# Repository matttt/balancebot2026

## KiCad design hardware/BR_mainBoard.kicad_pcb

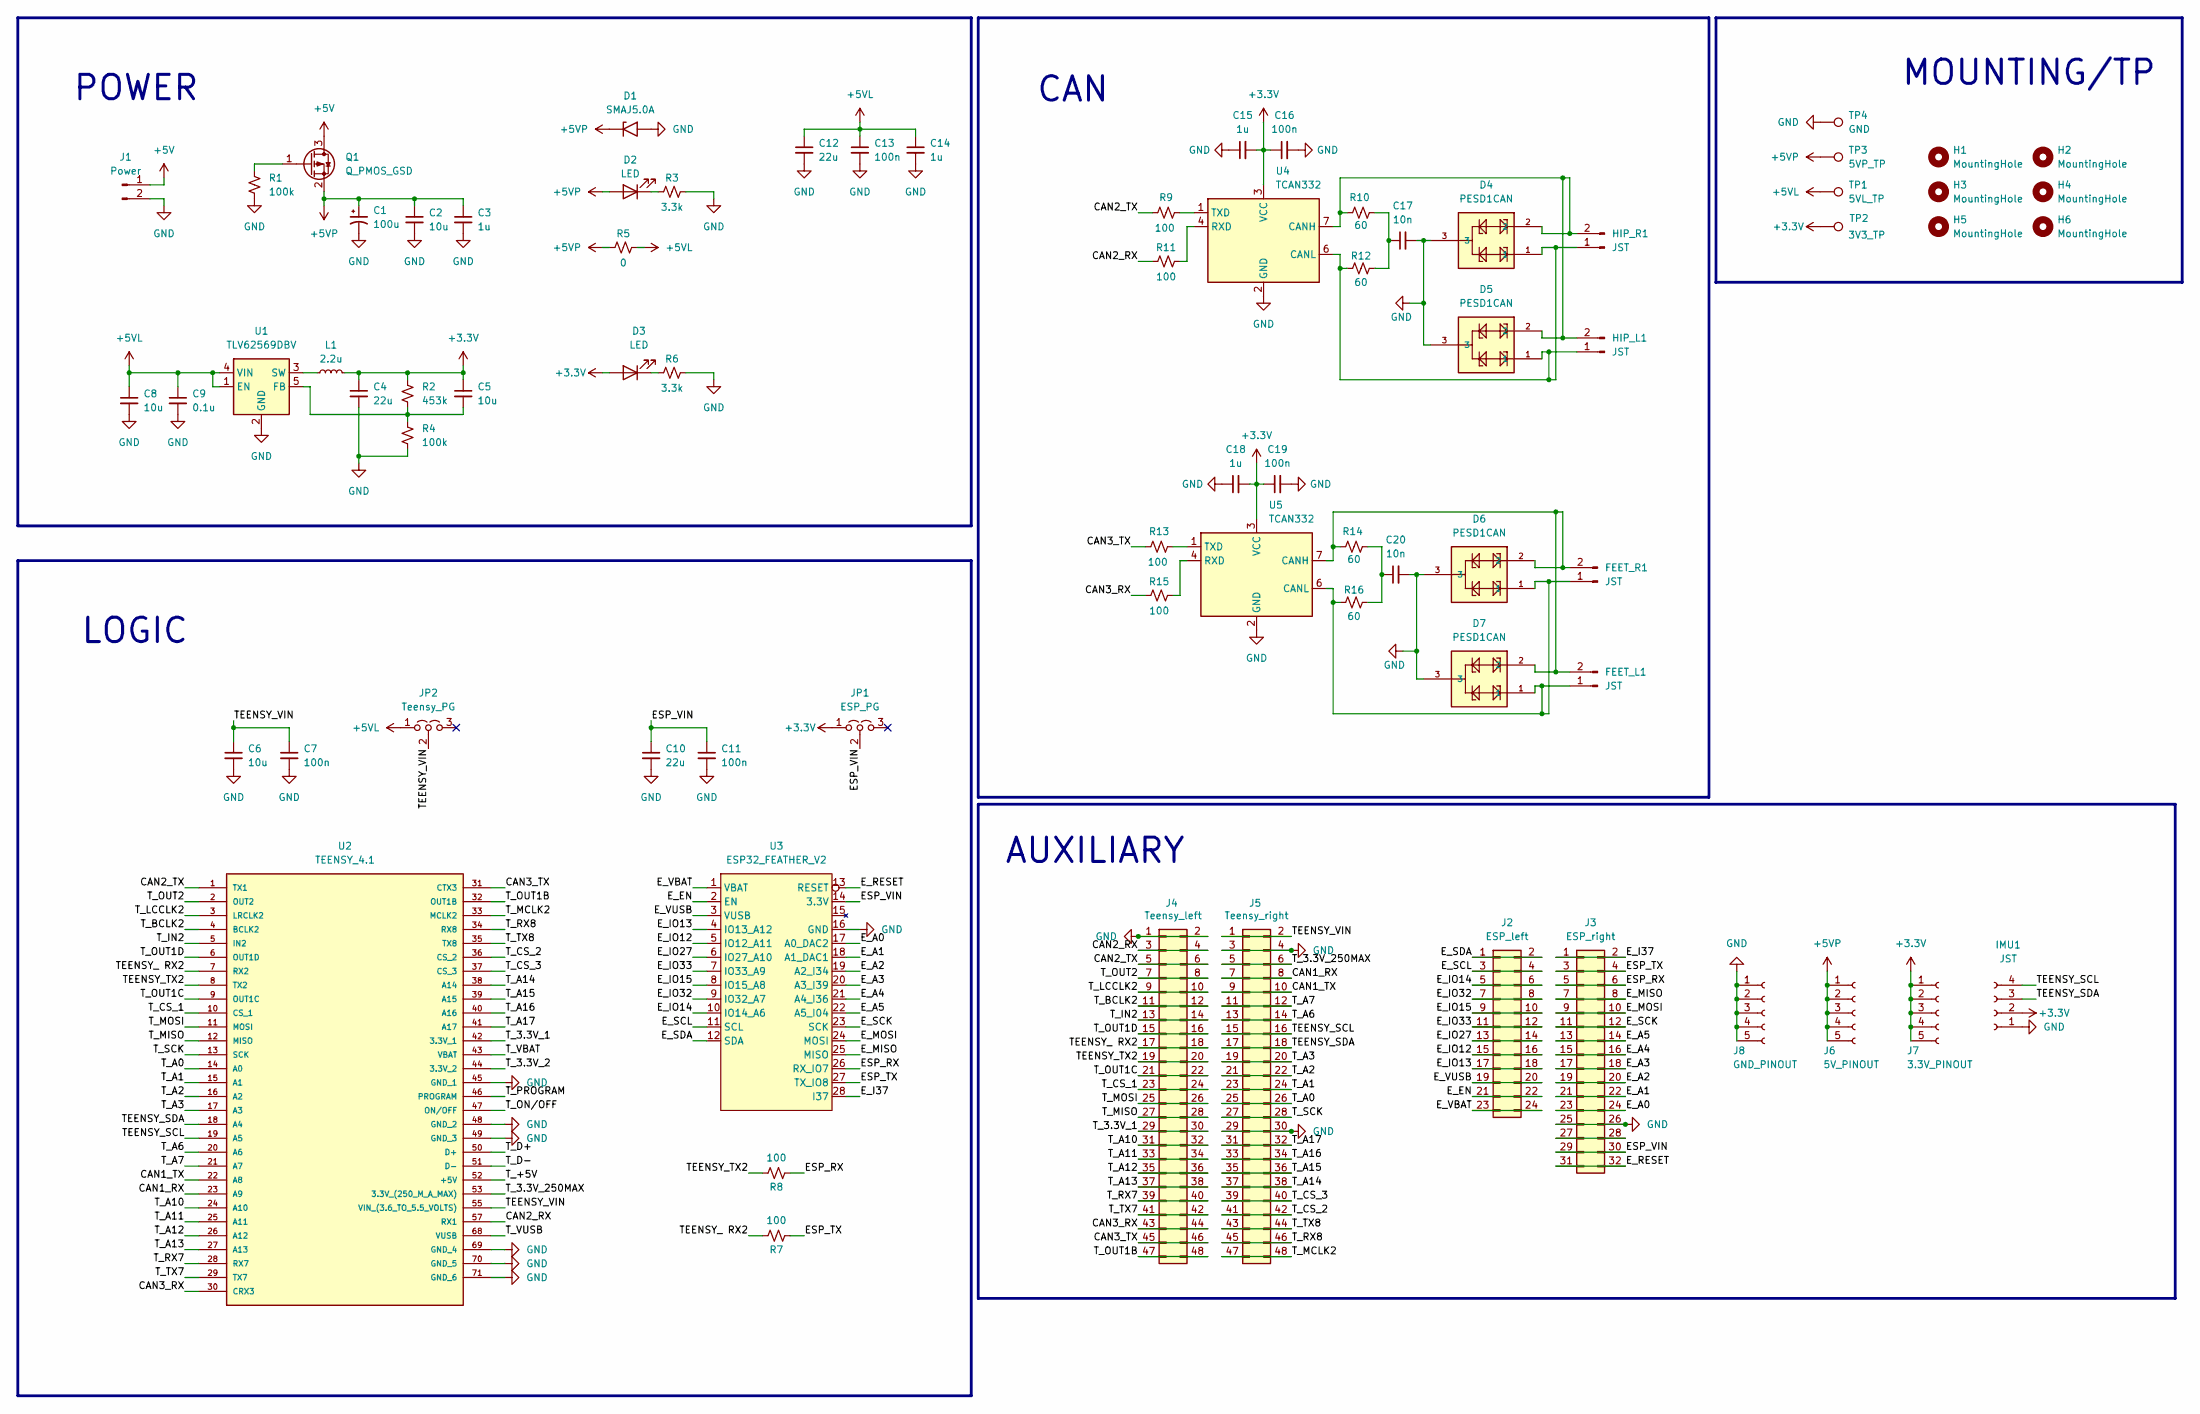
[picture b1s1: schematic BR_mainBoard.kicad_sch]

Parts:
C1: 100u; CP_Elec_6.3x5.4
C2, C5, C6, C8: 10u; C_1206_3216Metric
C3, C14, C15, C18: 1u; C_0805_2012Metric
C4, C10, C12: 22u; C_1206_3216Metric
C7, C11, C13, C16, C19: 100n; C_0805_2012Metric
C9: 0.1u; C_0805_2012Metric
C17, C20: 10n; C_0805_2012Metric
D1: SMAJ5.0A; D_SMA
D2, D3: LED; LED_0805_2012Metric
D4, D5, D6, D7: PESD1CAN; SOT-23
FEET_L1: JST; JST_VH_B2PS-VH_1x02_P3.96mm_Horizontal
FEET_R1: JST; JST_VH_B2PS-VH_1x02_P3.96mm_Horizontal
H1, H2, H3, H4, H5, H6: MountingHole; MountingHole_3.2mm_M3
HIP_L1: JST; JST_VH_B2PS-VH_1x02_P3.96mm_Horizontal
HIP_R1: JST; JST_VH_B2PS-VH_1x02_P3.96mm_Horizontal
IMU1: JST; JST_PH_S4B-PH-K_1x04_P2.00mm_Horizontal
J1: Power; JST_VH_B2P-VH-FB-B_1x02_P3.96mm_Vertical
J2: ESP_left; PinSocket_2x12_P2.54mm_Vertical
J3: ESP_right; PinSocket_2x16_P2.54mm_Vertical
J4: Teensy_left; PinSocket_2x24_P2.54mm_Vertical
J5: Teensy_right; PinSocket_2x24_P2.54mm_Vertical
J6: 5V_PINOUT; PinSocket_1x05_P2.54mm_Vertical
J7: 3.3V_PINOUT; PinSocket_1x05_P2.54mm_Vertical
J8: GND_PINOUT; PinSocket_1x05_P2.54mm_Vertical
JP1: ESP_PG; PinHeader_1x03_P2.54mm_Vertical
JP2: Teensy_PG; PinHeader_1x03_P2.54mm_Vertical
L1: 2.2u; L_Coilcraft_XAL4020-XXX
Q1: Q_PMOS_GSD; SOT-23
R1, R4: 100k; R_0805_2012Metric
R2: 453k; R_0805_2012Metric
R3, R6: 3.3k; R_0805_2012Metric
R5: 0; R_0805_2012Metric
R7, R8, R9, R11, R13, R15: 100; R_0805_2012Metric
R10, R12, R14, R16: 60; R_0603_1608Metric
TP1: 5VL_TP; TestPoint_Loop_D2.50mm_Drill1.0mm
TP2: 3V3_TP; TestPoint_Loop_D2.50mm_Drill1.0mm
TP3: 5VP_TP; TestPoint_Loop_D2.50mm_Drill1.0mm
TP4: GND; TestPoint_Loop_D2.50mm_Drill1.0mm
U1: TLV62569DBV; SOT-23-5
U2: TEENSY_4.1; TEENSY41; Manufacturer_Part_Number TEENSY 4.1
U3: ESP32_FEATHER_V2
U4, U5: TCAN332; SOIC-8_3.9x4.9mm_P1.27mm

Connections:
+3.3V: C4.1, C5.1, C15.2, C16.1, C18.2, C19.1, D3.2 (A), IMU1.2, J7.1, J7.2, J7.3, J7.4, J7.5, JP1.1 (A), L1.2, R2.1, TP2.1 (1_1), U4.3 (VCC), U5.3 (VCC)
+5V: J1.1, Q1.3 (D)
+5VL: C8.1, C9.1, C12.1, C13.1, C14.1, JP2.1 (A), R5.2, TP1.1 (1_1), U1.1 (EN), U1.4 (VIN)
+5VP: C1.1, C2.1, C3.1, D1.1 (A1), D2.2 (A), J6.1, J6.2, J6.3, J6.4, J6.5, Q1.2 (S), R5.1, TP3.1 (1_1)
/CAN1_RX: J5.7, J5.8, U2.23 (A9)
/CAN1_TX: J5.9, J5.10, U2.22 (A8)
/CAN2_RX: J4.3, J4.4, R11.1, U2.57 (RX1)
/CAN2_TX: J4.5, J4.6, R9.1, U2.1 (TX1)
/CAN3_RX: J4.43, J4.44, R15.1, U2.30 (CRX3)
/CAN3_TX: J4.45, J4.46, R13.1, U2.31 (CTX3)
/ESP_RX: J3.5, J3.6, R8.1, U3.26 (RX_IO7)
/ESP_TX: J3.3, J3.4, R7.1, U3.27 (TX_IO8)
/ESP_VIN: C10.1, C11.1, J3.29, J3.30, JP1.2 (C), U3.14 (3.3V)
/E_A0: J3.23, J3.24, U3.17 (A0_DAC2)
/E_A1: J3.21, J3.22, U3.18 (A1_DAC1)
/E_A2: J3.19, J3.20, U3.19 (A2_I34)
/E_A3: J3.17, J3.18, U3.20 (A3_I39)
/E_A4: J3.15, J3.16, U3.21 (A4_I36)
/E_A5: J3.13, J3.14, U3.22 (A5_I04)
/E_EN: J2.21, J2.22, U3.2 (EN)
/E_I37: J3.1, J3.2, U3.28 (I37)
/E_IO12: J2.15, J2.16, U3.5 (IO12_A11)
/E_IO13: J2.17, J2.18, U3.4 (IO13_A12)
/E_IO14: J2.5, J2.6, U3.10 (IO14_A6)
/E_IO15: J2.9, J2.10, U3.8 (IO15_A8)
/E_IO27: J2.13, J2.14, U3.6 (IO27_A10)
/E_IO32: J2.7, J2.8, U3.9 (IO32_A7)
/E_IO33: J2.11, J2.12, U3.7 (IO33_A9)
/E_MISO: J3.7, J3.8, U3.25 (MISO)
/E_MOSI: J3.9, J3.10, U3.24 (MOSI)
/E_RESET: J3.31, J3.32, U3.13 (RESET)
/E_SCK: J3.11, J3.12, U3.23 (SCK)
/E_SCL: J2.3, J2.4, U3.11 (SCL)
/E_SDA: J2.1, J2.2, U3.12 (SDA)
/E_VBAT: J2.23, J2.24, U3.1 (VBAT)
/E_VUSB: J2.19, J2.20, U3.3 (VUSB)
/TEENSY_ RX2: J4.17, J4.18, R7.2, U2.7 (RX2)
/TEENSY_SCL: IMU1.4, J5.15, J5.16, U2.19 (A5)
/TEENSY_SDA: IMU1.3, J5.17, J5.18, U2.18 (A4)
/TEENSY_TX2: J4.19, J4.20, R8.2, U2.8 (TX2)
/TEENSY_VIN: C6.1, C7.1, J5.1, J5.2, JP2.2 (C), U2.55 (VIN_(3.6_TO_5.5_VOLTS))
/T_3.3V_1: J4.29, J4.30, U2.42 (3.3V_1)
/T_3.3V_2: U2.44 (3.3V_2)
/T_3.3V_250MAX: J5.5, J5.6, U2.53 (3.3V_(250_M_A_MAX))
/T_+5V: U2.52 (+5V)
/T_A0: J5.25, J5.26, U2.14 (A0)
/T_A1: J5.23, J5.24, U2.15 (A1)
/T_A2: J5.21, J5.22, U2.16 (A2)
/T_A3: J5.19, J5.20, U2.17 (A3)
/T_A6: J5.13, J5.14, U2.20 (A6)
/T_A7: J5.11, J5.12, U2.21 (A7)
/T_A10: J4.31, J4.32, U2.24 (A10)
/T_A11: J4.33, J4.34, U2.25 (A11)
/T_A12: J4.35, J4.36, U2.26 (A12)
/T_A13: J4.37, J4.38, U2.27 (A13)
/T_A14: J5.37, J5.38, U2.38 (A14)
/T_A15: J5.35, J5.36, U2.39 (A15)
/T_A16: J5.33, J5.34, U2.40 (A16)
/T_A17: J5.31, J5.32, U2.41 (A17)
/T_BCLK2: J4.11, J4.12, U2.4 (BCLK2)
/T_CS_1: J4.23, J4.24, U2.10 (CS_1)
/T_CS_2: J5.41, J5.42, U2.36 (CS_2)
/T_CS_3: J5.39, J5.40, U2.37 (CS_3)
/T_D+: U2.50 (D+)
/T_D-: U2.51 (D-)
/T_IN2: J4.13, J4.14, U2.5 (IN2)
/T_LCCLK2: J4.9, J4.10, U2.3 (LRCLK2)
/T_MCLK2: J5.47, J5.48, U2.33 (MCLK2)
/T_MISO: J4.27, J4.28, U2.12 (MISO)
/T_MOSI: J4.25, J4.26, U2.11 (MOSI)
/T_ON/OFF: U2.47 (ON/OFF)
/T_OUT1B: J4.47, J4.48, U2.32 (OUT1B)
/T_OUT1C: J4.21, J4.22, U2.9 (OUT1C)
/T_OUT1D: J4.15, J4.16, U2.6 (OUT1D)
/T_OUT2: J4.7, J4.8, U2.2 (OUT2)
/T_PROGRAM: U2.46 (PROGRAM)
/T_RX7: J4.39, J4.40, U2.28 (RX7)
/T_RX8: J5.45, J5.46, U2.34 (RX8)
/T_SCK: J5.27, J5.28, U2.13 (SCK)
/T_TX7: J4.41, J4.42, U2.29 (TX7)
/T_TX8: J5.43, J5.44, U2.35 (TX8)
/T_VBAT: U2.43 (VBAT)
/T_VUSB: U2.68 (VUSB)
GND: C1.2, C2.2, C3.2, C4.2, C6.2, C7.2, C8.2, C9.2, C10.2, C11.2, C12.2, C13.2, C14.2, C15.1, C16.2, C17.2, C18.1, C19.2, C20.2, D1.2 (A2), D4.3, D5.3, D6.3, D7.3, IMU1.1, J1.2, J3.25, J3.26, J4.1, J4.2, J5.3, J5.4, J5.29, J5.30, J8.1, J8.2, J8.3, J8.4, J8.5, R1.2, R3.2, R4.2, R6.2, TP4.1 (1_1), U1.2 (GND), U2.45 (GND_1), U2.48 (GND_2), U2.49 (GND_3), U2.69 (GND_4), U2.70 (GND_5), U2.71 (GND_6), U3.16 (GND), U4.2 (GND), U5.2 (GND)
unnamed: C17.1, R10.2, R12.2
unnamed: C20.1, R14.2, R16.2
unnamed: D2.1 (K), R3.1
unnamed: D3.1 (K), R6.1
unnamed: D6.1, D7.1, FEET_L1.1, FEET_R1.1, R16.1, U5.6 (CANL)
unnamed: D6.2, D7.2, FEET_L1.2, FEET_R1.2, R14.1, U5.7 (CANH)
unnamed: D4.1, D5.1, HIP_L1.1, HIP_R1.1, R12.1, U4.6 (CANL)
unnamed: D4.2, D5.2, HIP_L1.2, HIP_R1.2, R10.1, U4.7 (CANH)
unnamed: J3.27, J3.28
unnamed: Q1.1 (G), R1.1
unnamed: C5.2, R2.2, R4.1, U1.5 (FB)
unnamed: L1.1, U1.3 (SW)
unnamed: R11.2, U4.4 (RXD)
unnamed: R9.2, U4.1 (TXD)
unnamed: R15.2, U5.4 (RXD)
unnamed: R13.2, U5.1 (TXD)

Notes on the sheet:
CAN
MOUNTING/TP
LOGIC
POWER
AUXILIARY

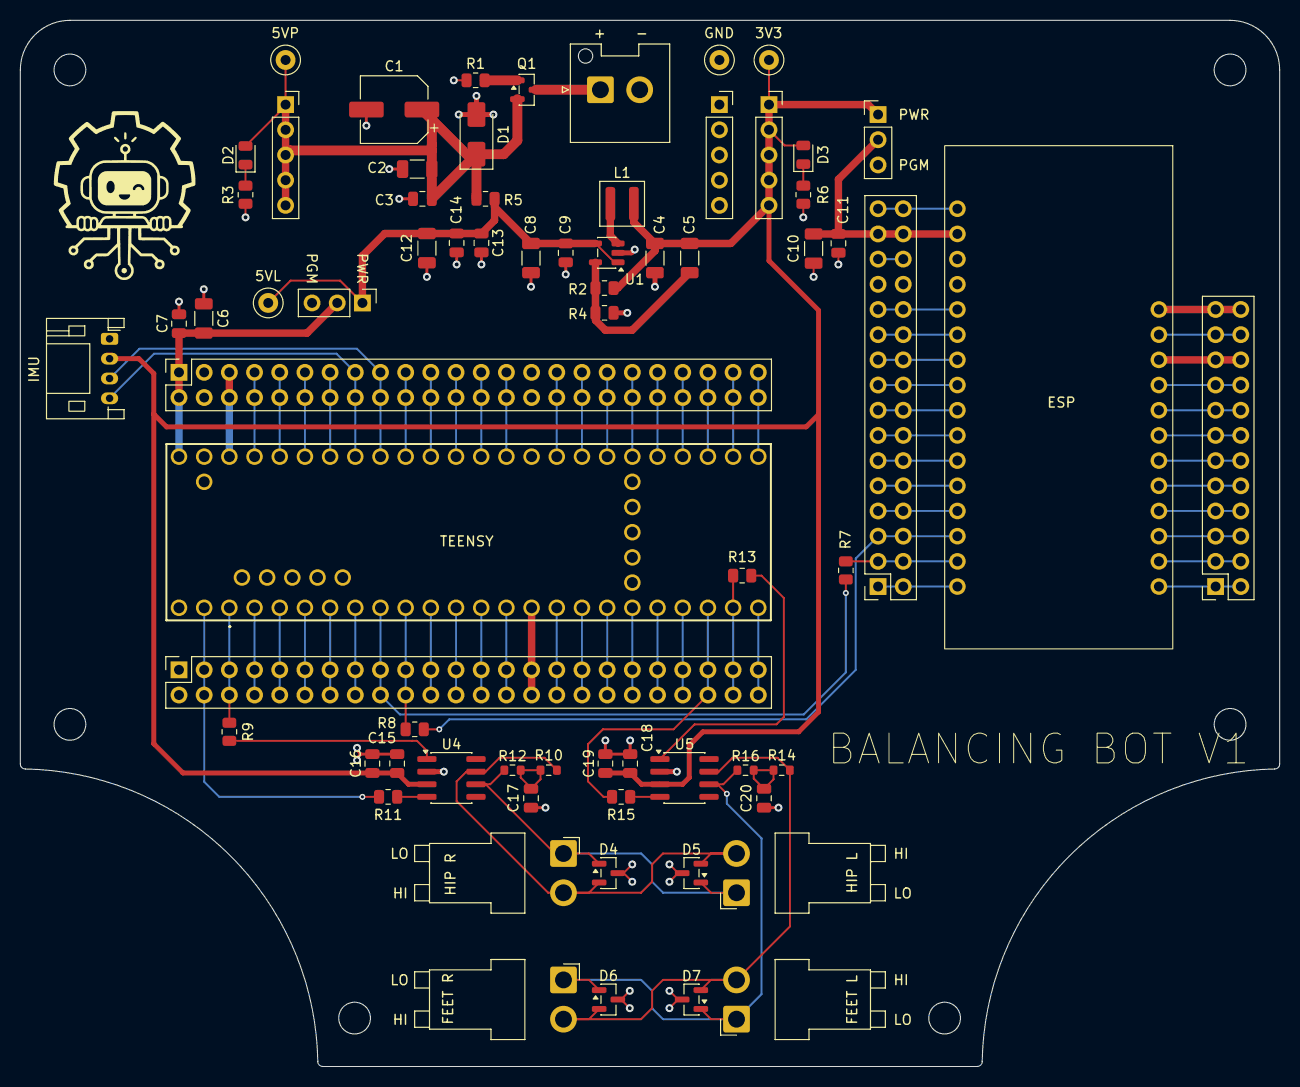
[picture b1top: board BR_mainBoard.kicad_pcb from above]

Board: 2 copper layers, 127.0 x 105.5 mm, 75 parts (0 on the bottom side), 92 nets.

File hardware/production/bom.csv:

Designator,Footprint,Quantity,Value,LCSC Part #
C1,CP_Elec_6.3x5.4,1,100u,
"C10, C12, C4",1206,3,22u,
"C11, C13, C16, C19, C7",0805,5,100n,
"C14, C15, C18, C3",0805,4,1u,
"C17, C20",0805,2,10n,
"C2, C5, C6, C8",1206,4,10u,
C9,0805,1,0.1u,
D1,D_SMA,1,SMAJ5.0A,
"D2, D3",0805,2,LED,
"D4, D5, D6, D7",SOT-23,4,PESD1CAN,
"FEET_L1, FEET_R1, HIP_L1, HIP_R1",JST_VH_B2PS-VH_1x02_P3.96mm_Horizontal,4,JST,
IMU1,JST_PH_S4B-PH-K_1x04_P2.00mm_Horizontal,1,JST,
J1,JST_VH_B2P-VH-FB-B_1x02_P3.96mm_Vertical,1,Power,
J2,PinSocket_2x12_P2.54mm_Vertical,1,ESP_left,
J3,PinSocket_2x16_P2.54mm_Vertical,1,ESP_right,
J4,PinSocket_2x24_P2.54mm_Vertical,1,Teensy_left,
J5,PinSocket_2x24_P2.54mm_Vertical,1,Teensy_right,
J6,PinSocket_1x05_P2.54mm_Vertical,1,5V_PINOUT,
J7,PinSocket_1x05_P2.54mm_Vertical,1,3.3V_PINOUT,
J8,PinSocket_1x05_P2.54mm_Vertical,1,GND_PINOUT,
JP1,PinHeader_1x03_P2.54mm_Vertical,1,ESP_PG,
JP2,PinHeader_1x03_P2.54mm_Vertical,1,Teensy_PG,
L1,L_Coilcraft_XAL4020-XXX,1,2.2u,
Q1,SOT-23,1,Q_PMOS_GSD,
"R1, R4",0805,2,100k,
"R10, R12, R14, R16",0603,4,60,
"R11, R13, R15, R7, R8, R9",0805,6,100,
R2,0805,1,453k,
"R3, R6",0805,2,3.3k,
R5,0805,1,0,
U1,SOT-23-5,1,TLV62569DBV,
"U4, U5",SOIC-8_3.9x4.9mm_P1.27mm,2,TCAN332,

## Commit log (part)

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2026-02-16 init commit with basic esp32 firmware example for can communication
2026-02-16 structure
2026-02-17 hip actuator demo
    basic demo that shows sine wave behavior with actuator. Formalizes basic CAN structure.
2026-02-17 fucked up folder structure
2026-02-23 take main.cpp to a simple wifi ap with a config page
2026-02-23 change esp firmware folder name
2026-02-23 add meter-unit'd objs
2026-02-25 added pio structure to teensy
2026-02-25 added test and include
    github does not like 'test' folder
2026-02-28 Add webots sim and two-wheeled inverted pendulum analysis model
2026-02-28 Add WheeledBipedSim README
2026-03-03 added esp_teensy_comm.cpp
    created esp_teensy_comm.cpp to interface with teensy, currently runs as a sine wave demo with proper hardware connected.
2026-04-13 Added BNO-055 IMU support
2026-05-23 EKF test working
2026-05-25 serial cli for rob stride motor
2026-05-25 rest of previous
2026-06-08 All demos working
